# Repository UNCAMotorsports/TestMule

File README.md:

# RedBuggy
Software related to the "Red Buggy" / FSAE car for UNCA Motorsports

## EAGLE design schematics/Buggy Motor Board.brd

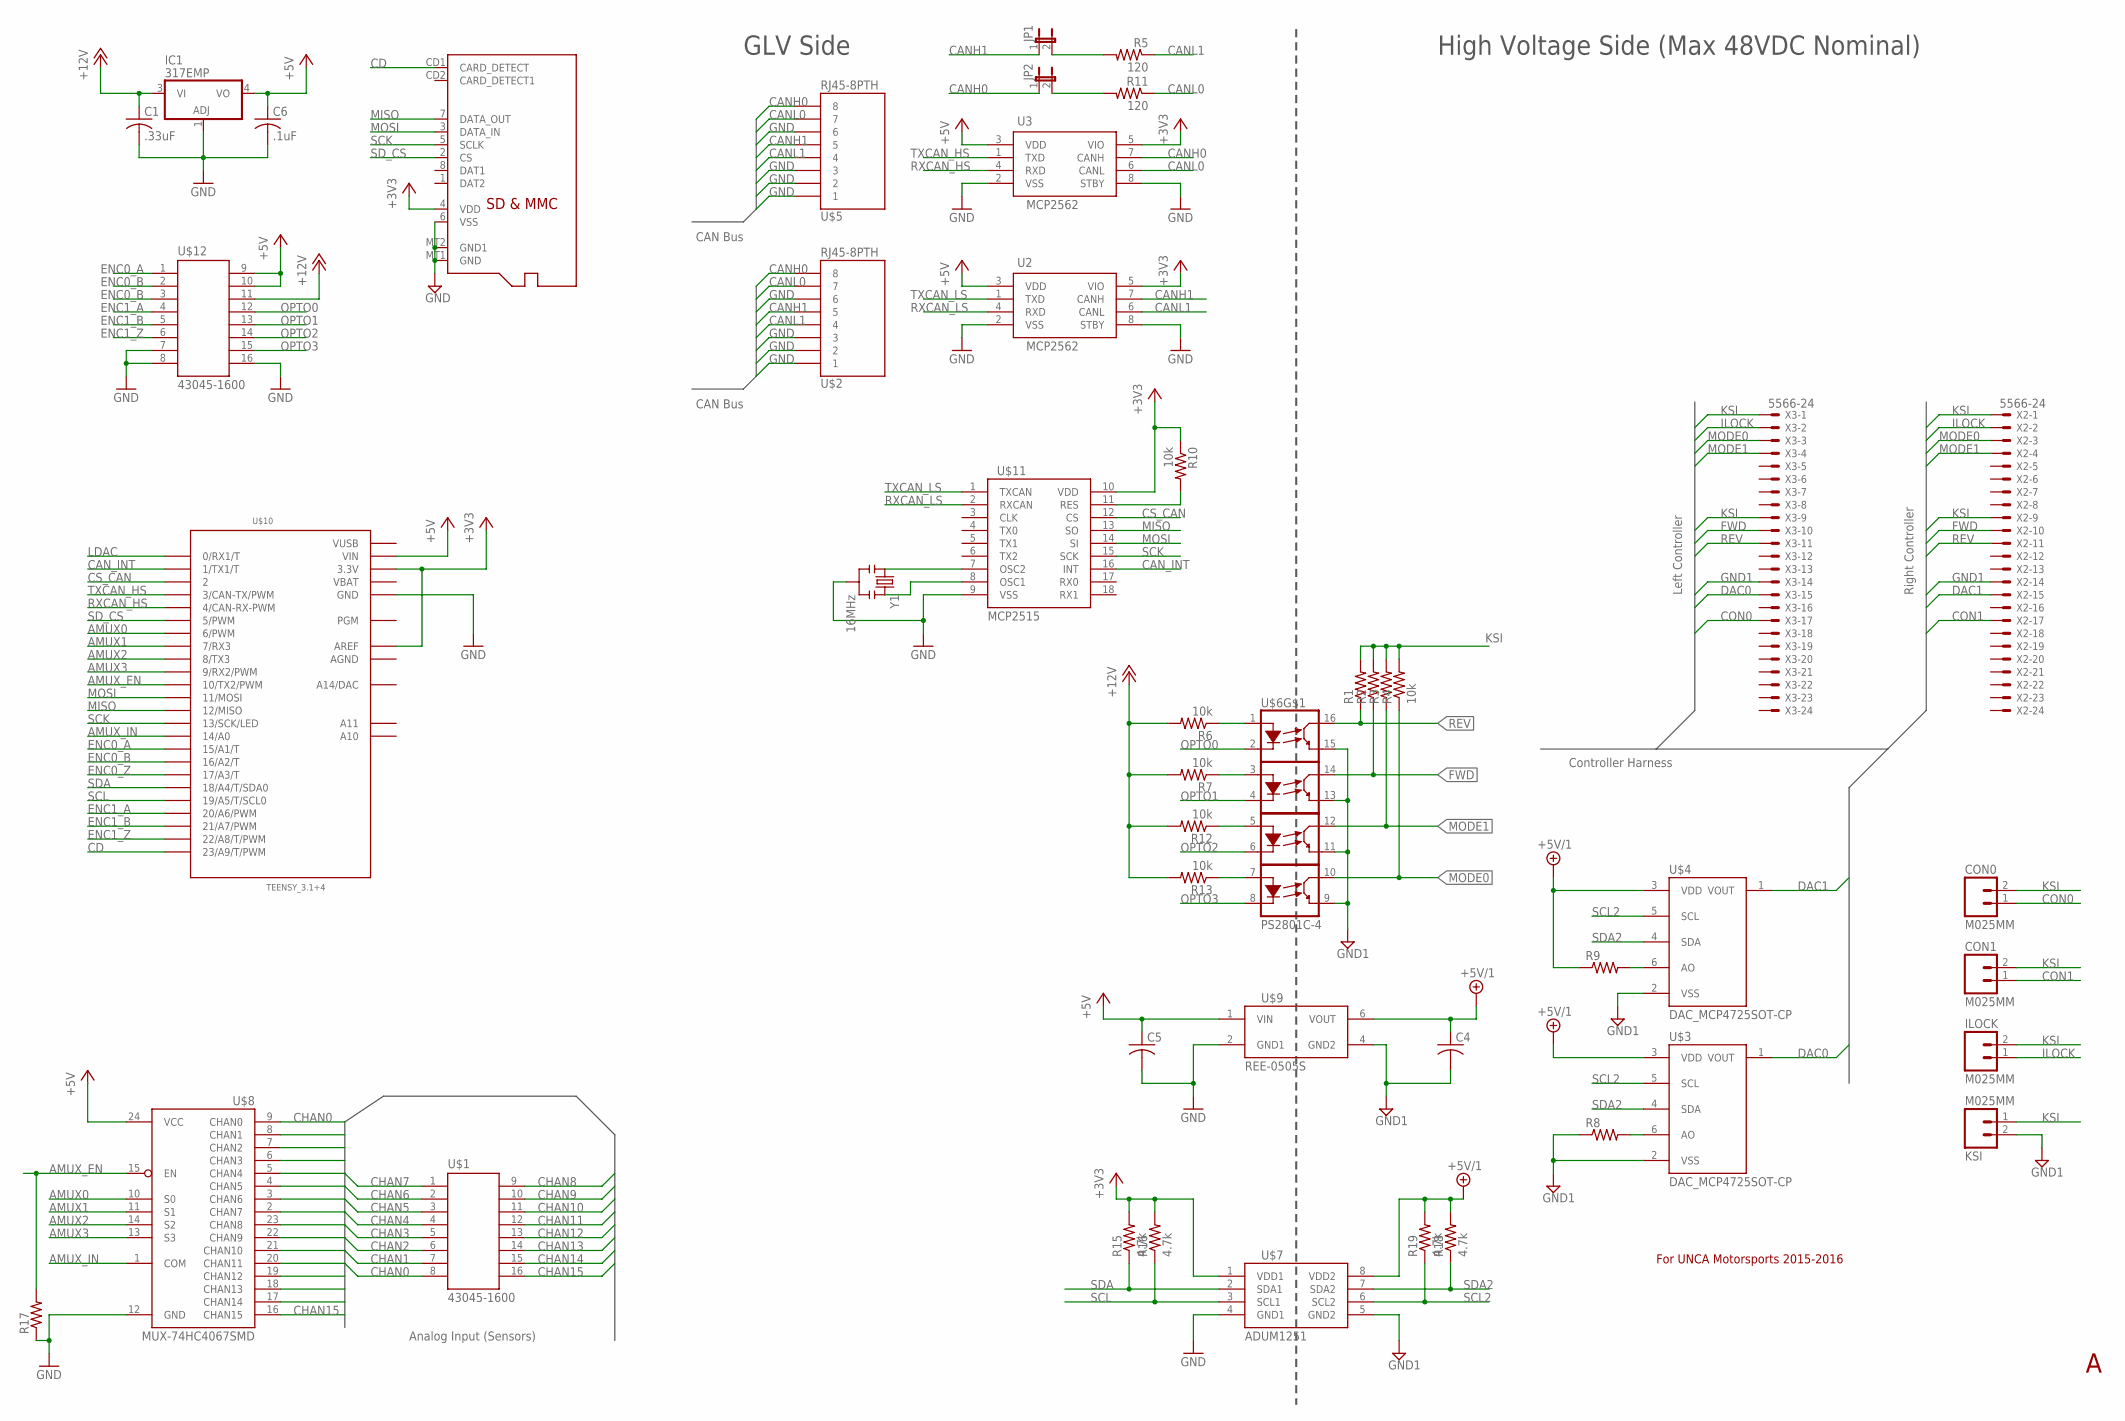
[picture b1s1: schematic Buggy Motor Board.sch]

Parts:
C1: .33uF; C0805
C4, C5: C-USC1210K; C1210K
C6: .1uF; C0805
CON0, CON1: M025MM; SCREWTERMINAL-5MM-2
IC1: 317EMP; SOT223
ILOCK: M025MM; SCREWTERMINAL-5MM-2
JP1, JP2: JP1E; JP1
KSI: M025MM; SCREWTERMINAL-5MM-2
R1, R2, R3, R8, R9, R17: RESISTOR0805-RES; 0805
R4, R6, R7, R10, R12, R13: 10k; 0805
R5, R11: 120; 0805
R15, R16, R18, R19: 4.7k; 0805
U2, U3: MCP2562; SO08
U$1, U$12: 43045-1600
U$2, U$5: RJ45-8PTH; RJ45-8
U$3, U$4: DAC_MCP4725SOT-CP; SOT23-6-MCP4725
U$6: PS2801C-4; 16-SOIC
U$7: ADUM1251; 8-SOIC
U$8: MUX-74HC4067SMD; SSOP24
U$9: REE-0505S
U$10: TEENSY_3.1+4
U$11: MCP2515; DIL18
X1: MICROSD
X2, X3: 5566-24
Y1: 16MHz; RESONATOR-PTH

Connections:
+3V3: R10.1, R15.2, R16.2, U2.5 (VIO), U3.5 (VIO), U$7.1 (VDD1), U$10.3.3V, U$10.3.3V1 (3.3V), U$10.AREF, U$11.10 (VDD), X1.4 (VDD)
+5V: C5.1, C6.1, IC1.4 (VO), U2.3 (VDD), U3.3 (VDD), U$8.24 (VCC), U$9.1 (VIN), U$10.VIN, U$12.9, U$12.10
+5V/1: C4.1, R9.1, R18.2, R19.2, U$3.3 (VDD), U$4.3 (VDD), U$7.8 (VDD2), U$9.6 (VOUT)
+12V: C1.1, IC1.3 (VI), R6.2, R7.2, R12.2, R13.2, U$12.11
AGND: U$10.AGND
AMUX0: U$8.10 (S0), U$10.6 (6/PWM)
AMUX1: U$8.11 (S1), U$10.7 (7/RX3)
AMUX2: U$8.14 (S2), U$10.8 (8/TX3)
AMUX3: U$8.13 (S3), U$10.9 (9/RX2/PWM)
AMUX_EN: R17.2, U$8.15 (EN), U$10.10 (10/TX2/PWM)
AMUX_IN: U$8.1 (COM), U$10.14/A0
CANH0: JP2.1, U3.7 (CANH), U$2.8, U$5.8
CANH1: JP1.1, U2.7 (CANH), U$2.5, U$5.5
CANL0: R11.1, U3.6 (CANL), U$2.7, U$5.7
CANL1: R5.1, U2.6 (CANL), U$2.4, U$5.4
CAN_INT: U$10.1 (1/TX1/T), U$11.16 (INT)
CD: U$10.23/A9 (23/A9/T/PWM), X1.CD1 (CARD_DETECT)
CHAN0: U$1.8, U$8.9 (CHAN0)
CHAN1: U$1.7, U$8.8 (CHAN1)
CHAN2: U$1.6, U$8.7 (CHAN2)
CHAN3: U$1.5, U$8.6 (CHAN3)
CHAN4: U$1.4, U$8.5 (CHAN4)
CHAN5: U$1.3, U$8.4 (CHAN5)
CHAN6: U$1.2, U$8.3 (CHAN6)
CHAN7: U$1.1, U$8.2 (CHAN7)
CHAN8: U$1.9, U$8.23 (CHAN8)
CHAN9: U$1.10, U$8.22 (CHAN9)
CHAN10: U$1.11, U$8.21 (CHAN10)
CHAN11: U$1.12, U$8.20 (CHAN11)
CHAN12: U$1.13, U$8.19 (CHAN12)
CHAN13: U$1.14, U$8.18 (CHAN13)
CHAN14: U$1.15, U$8.17 (CHAN14)
CHAN15: U$1.16, U$8.16 (CHAN15)
CON0: CON0.1, X3.17
CON1: CON1.1, X2.17
CS_CAN: U$10.2, U$11.12 (CS)
DAC0: U$3.1 (VOUT), X3.15
DAC1: U$4.1 (VOUT), X2.15
ENC0_A: U$10.15/A1 (15/A1/T), U$12.1
ENC0_B: U$10.16/A2 (16/A2/T), U$12.2
ENC0_Z: U$10.17/A3 (17/A3/T), U$12.3
ENC1_A: U$10.20/A6 (20/A6/PWM), U$12.4
ENC1_B: U$10.21/A7 (21/A7/PWM), U$12.5
ENC1_Z: U$10.22/A8 (22/A8/T/PWM), U$12.6
FWD: R2.1, U$6.14 (L1), X2.10, X3.10
GND: C1.2, C5.2, C6.2, IC1.1 (ADJ), R17.1, U2.2 (VSS), U2.8 (STBY), U3.2 (VSS), U3.8 (STBY), U$2.1, U$2.2, U$2.3, U$2.6, U$5.1, U$5.2, U$5.3, U$5.6, U$7.4 (GND1), U$8.12 (GND), U$9.2 (GND1), U$10.GND, U$10.GND1 (GND), U$11.9 (VSS), U$12.7, U$12.8, U$12.16, X1.6 (VSS), X1.MT1 (GND), X1.MT2 (GND1), Y1.2
GND1: C4.2, KSI.2, R8.1, U$3.2 (VSS), U$4.2 (VSS), U$6.9 (L2), U$6.11 (L2), U$6.13 (L2), U$6.15 (L2), U$7.5 (GND2), U$9.4 (GND2), X2.14, X3.14
ILOCK: ILOCK.1, X2.2, X3.2
KSI: CON0.2, CON1.2, ILOCK.2, KSI.1, R1.2, R2.2, R3.2, R4.2, X2.1, X2.9, X3.1, X3.9
LDAC: U$10.0 (0/RX1/T)
MISO: U$10.12 (12/MISO), U$11.13 (SO), X1.7 (DATA_OUT)
MODE0: R4.1, U$6.10 (L1), X2.3, X3.3
MODE1: R3.1, U$6.12 (L1), X2.4, X3.4
MOSI: U$10.11 (11/MOSI), U$11.14 (SI), X1.3 (DATA_IN)
unnamed: JP1.2, R5.2
unnamed: R8.2, U$3.6 (AO)
unnamed: R9.2, U$4.6 (AO)
unnamed: U$11.7 (OSC2), Y1.1
unnamed: U$11.8 (OSC1), Y1.3
unnamed: R6.1, U$6.1 (A)
unnamed: JP2.2, R11.2
unnamed: R10.2, U$11.11 (RES)
unnamed: R7.1, U$6.3 (A)
unnamed: R12.1, U$6.5 (A)
unnamed: R13.1, U$6.7 (A)
OPTO0: U$6.2 (C), U$12.12
OPTO1: U$6.4 (C), U$12.13
OPTO2: U$6.6 (C), U$12.14
OPTO3: U$6.8 (C), U$12.15
REV: R1.1, U$6.16 (L1), X2.11, X3.11
RXCAN_HS: U3.4 (RXD), U$10.4 (4/CAN-RX-PWM)
RXCAN_LS: U2.4 (RXD), U$11.2 (RXCAN)
SCK: U$10.13 (13/SCK/LED), U$11.15 (SCK), X1.5 (SCLK)
SCL: R16.1, U$7.3 (SCL1), U$10.19/A5 (19/A5/T/SCL0)
SCL2: R19.1, U$3.5 (SCL), U$4.5 (SCL), U$7.6 (SCL2)
SDA: R15.1, U$7.2 (SDA1), U$10.18/A4 (18/A4/T/SDA0)
SDA2: R18.1, U$3.4 (SDA), U$4.4 (SDA), U$7.7 (SDA2)
SD_CS: U$10.5 (5/PWM), X1.2 (CS)
TXCAN_HS: U3.1 (TXD), U$10.3 (3/CAN-TX/PWM)
TXCAN_LS: U2.1 (TXD), U$11.1 (TXCAN)
VBAT: U$10.VBAT
VUSB: U$10.VUSB

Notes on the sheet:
For UNCA Motorsports 2015-2016
Analog Input (Sensors)
CAN Bus
Controller Harness
Left Controller
Right Controller
High Voltage Side (Max 48VDC Nominal)
GLV Side

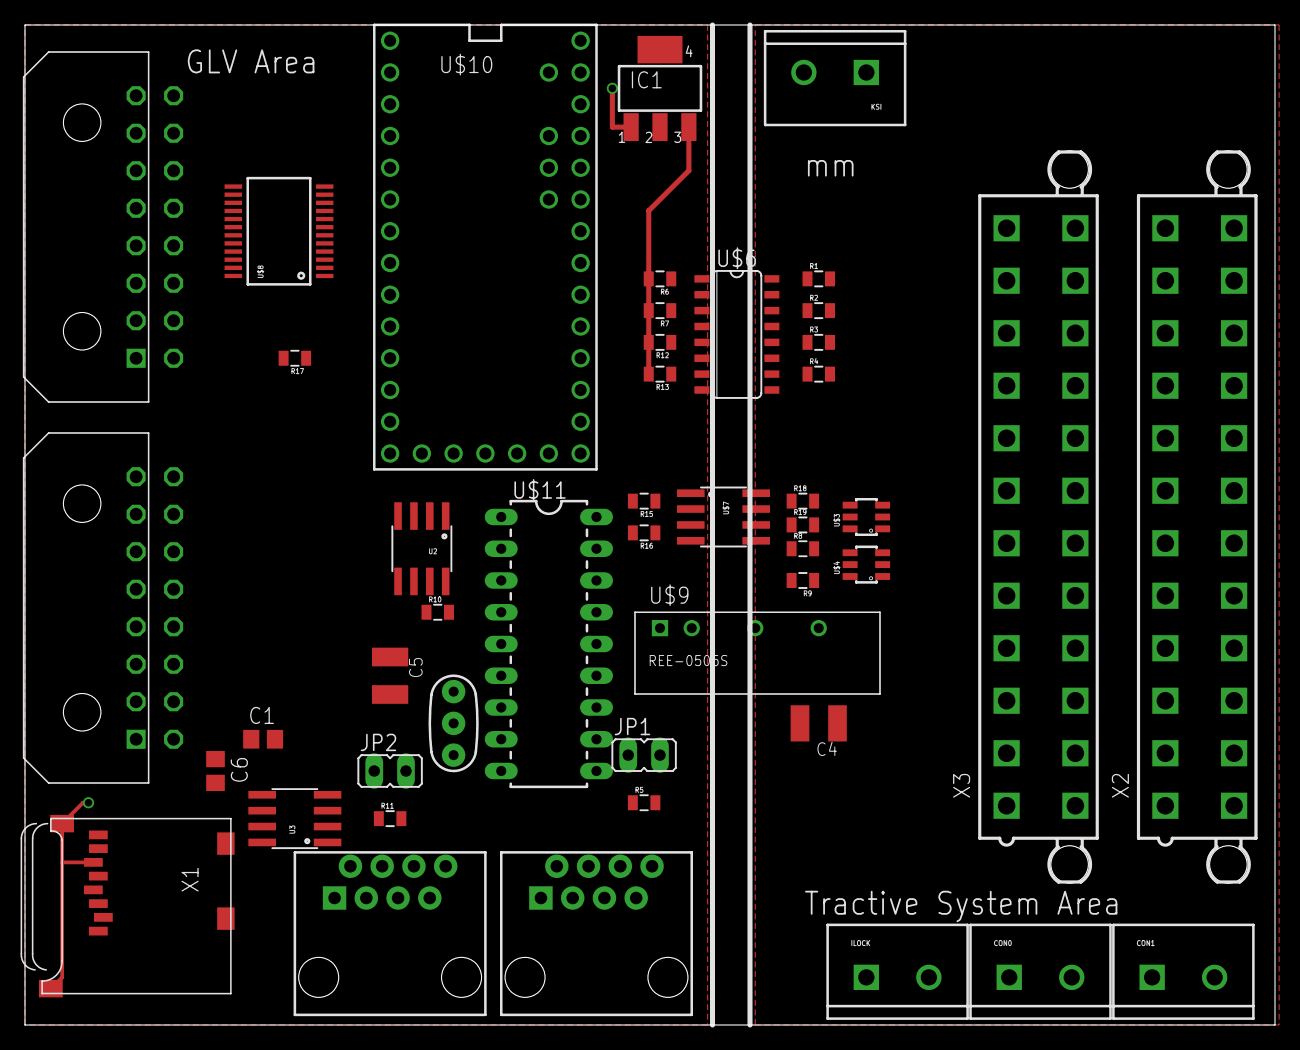
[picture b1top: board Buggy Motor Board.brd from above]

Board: 2 copper layers, 100.0 x 80.0 mm, 47 parts (0 on the bottom side), 78 nets.

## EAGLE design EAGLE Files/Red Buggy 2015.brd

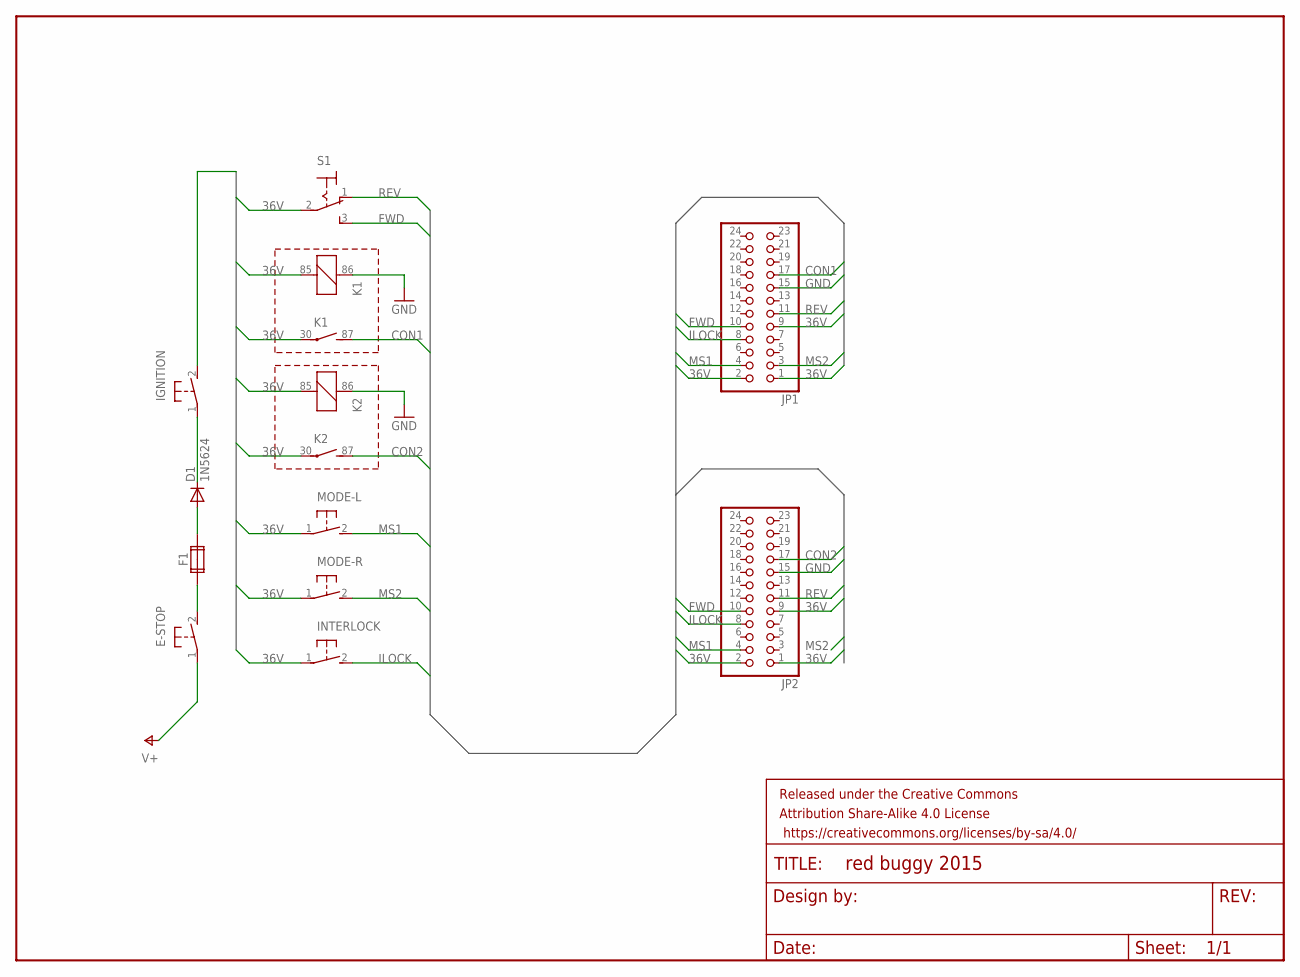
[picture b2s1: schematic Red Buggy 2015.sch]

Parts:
D1: 1N5624; DO201-15
E-STOP: 31-XX; B3F-31XX
F1: FUSE2P; FUSE1
FRAME1: FRAME-LETTER; CREATIVE_COMMONS
IGNITION: 31-XX; B3F-31XX
INTERLOCK: 31-XX; B3F-31XX
JP1, JP2: PINHD-2X12; 2X12
K1, K2: CB1A-P-12V; CB1
MODE-L: 31-XX; B3F-31XX
MODE-R: 31-XX; B3F-31XX
S1: 320-916

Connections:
36V: IGNITION.2 (S), INTERLOCK.1, JP1.1, JP1.2, JP1.9, JP2.1, JP2.2, JP2.9, K1.30, K1.85 (2), K2.30, K2.85 (2), MODE-L.1, MODE-R.1, S1.2
CON1: JP1.17, K1.87 (S)
CON2: JP2.17, K2.87 (S)
FWD: JP1.10, JP2.10, S1.3 (S)
GND: JP1.15, JP2.15, K1.86 (1), K2.86 (1)
ILOCK: INTERLOCK.2 (S), JP1.8, JP2.8
MS1: JP1.4, JP2.4, MODE-L.2 (S)
MS2: JP1.3, MODE-R.2 (S)
unnamed: D1.A, F1.2A
unnamed: E-STOP.2 (S), F1.1A
unnamed: D1.C, IGNITION.1
REV: JP1.11, JP2.11, S1.1 (O)
V+: E-STOP.1

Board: 2 copper layers, 13 parts (0 on the bottom side), 12 nets, no tracks yet.

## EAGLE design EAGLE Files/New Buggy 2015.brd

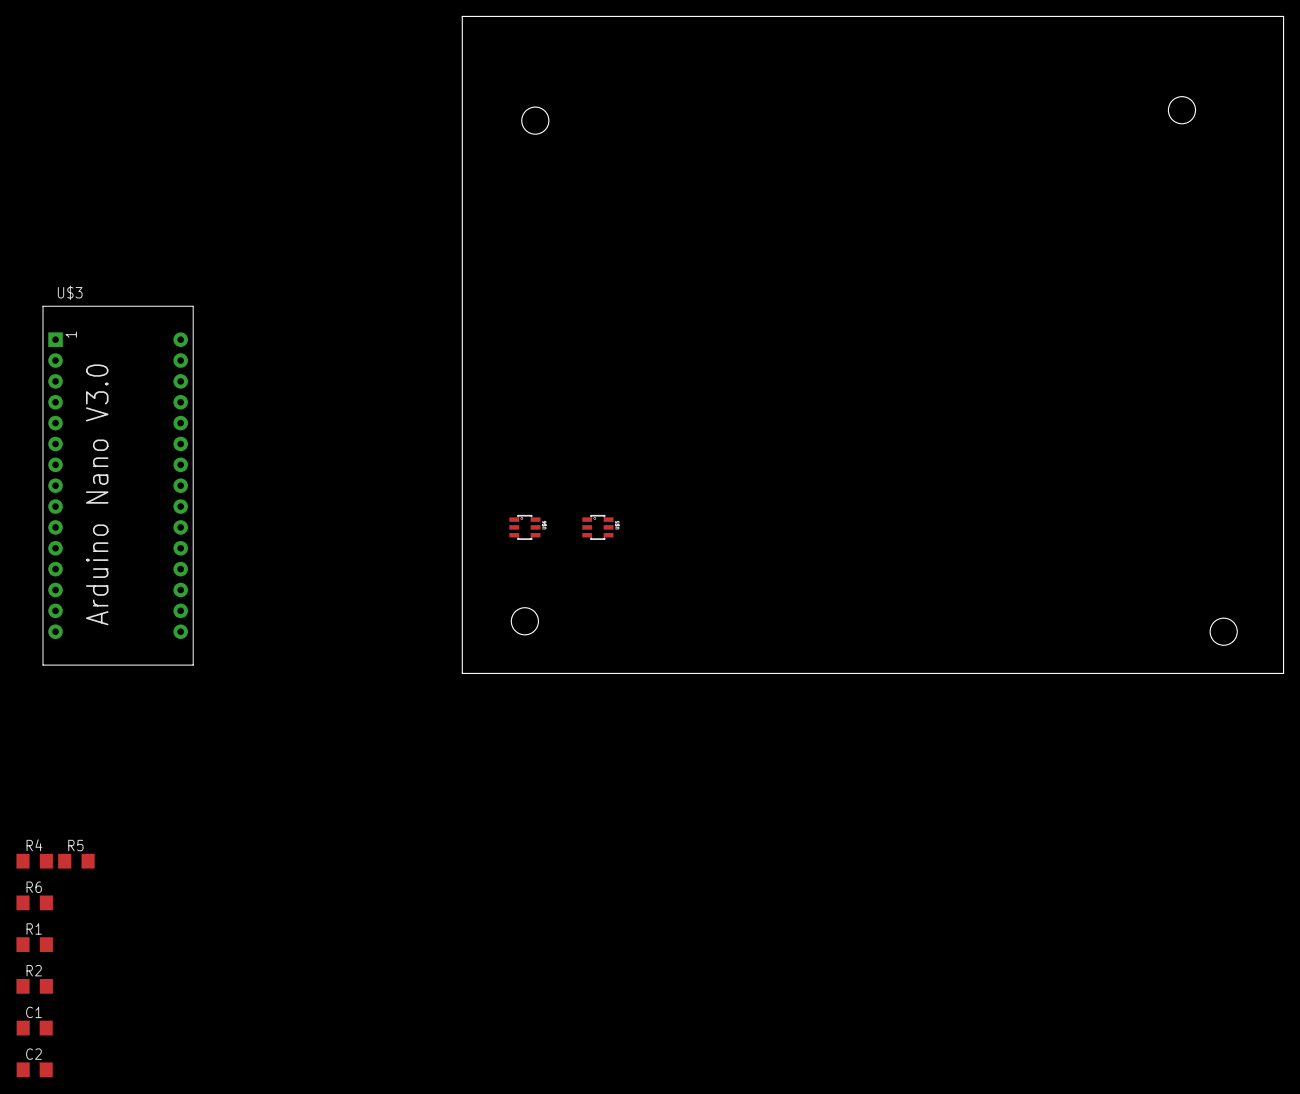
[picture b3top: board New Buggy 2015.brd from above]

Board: 2 copper layers, 100.0 x 80.0 mm, 14 parts (0 on the bottom side), 5 nets, no tracks yet.

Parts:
C1, C2: C1206
R1, R2, R4, R5, R6: R1206
STANDOFF1, STANDOFF2, STANDOFF3, STANDOFF4: STAND-OFF
U$3: ARDUINO_NANO
U$5, U$6: DAC_MCP4725SOT-CP; SOT23-6-MCP4725

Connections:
+5V: C1.1, C2.1, R1.1, R2.1, R4.1, R5.1, R6.1, U$3.+5V, U$5.3, U$6.3
GND: C1.2, C2.2, U$3.GND, U$3.GND@1, U$5.2, U$5.6, U$6.2
unnamed: R6.2, U$6.6
SCL: R1.2, R4.2, U$3.SCL*, U$5.5, U$6.5
SDA: R2.2, R5.2, U$3.SDA, U$5.4, U$6.4

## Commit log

2015-06-26 Actual Initial
2015-06-26 Testing pull requests
2015-06-30 Add sdf to gitignore
2015-06-30 More gitignore
2015-07-04 Add Old Code
2015-07-11 Control System docs init
2015-07-11 EAGLE Schematic init
2015-07-11 Added shift register (TEST)
2015-07-11 Added Screw Clamp (TEST)
2015-07-12 CAN Bus testing (Send/recv)
2015-07-14 CAN implementation
2015-07-20 Add CAN support to schematic, high side drivers.
2015-07-20 Interesting Red Buggy data
2015-07-22 Add SD Card slot & level shifter
2015-07-23 SourceTree test with Github
2015-07-24 Add analog multiplexer, shift register
2015-07-24 Add frame
2015-07-24 Optoisolators, MPU9150, cleanup
2015-07-24 Second shift register
2015-07-25 Saved with 25-07-2015 Visual Micro
2015-07-26 Second optocoupler
2015-07-26 Add molex connectors for curtis controllers
2015-07-27 Organization
2015-07-28 Tweak for Red Buggy
    Removed IMU, second opto-coupler, shift registers; added connectors for
    Curtis motor controllers
2015-07-28 Fix Libraries
2015-07-28 Rebuild
2015-07-29 Start Board, improve isolation
    Started layout of board. Changed Optocoupler. Improved isolation by
    moving DACs to the high voltage side and providing an isolated 5v rail.
    Added Isolated I2C Converter to communicate with DACs across airgap.
2015-08-02 Power consumption, analog input connectors
2015-08-04 Libraries
2015-08-04 Replace Nano with Teensy 3.1
2015-08-05 Add microfit connector
2015-08-05 Microfit connector
2015-08-06 Tweaks
2015-08-07 5v Optocoupling
2015-09-07 Pre-Share Update
2015-09-07 Demo
2015-09-08 Upgrade to newest Visual Micro
2015-09-08 Remove 3v3 level shifter, add encoder inputs
2015-09-08 Remove legacy code
    Code was a cluster of outdated Visual Micro, etc. CLeaning up.
2015-09-08 Move some stuff around
2015-09-08 Moving
2015-09-08 Add *.b#* to gitignore
2015-09-08 Tweak for Master
2015-09-08 Add Quadrature Counter, RTC, MPU, CAN Bus 2
2015-09-12 Schematic changes
2015-09-12 gitIgnore
2015-09-12 remove sdf
2015-09-12 Implement steering code
2015-09-12 Comments, latch
2015-09-20 Teensy changes, working code
2015-09-26 Debug defines
2015-10-18 Tested to be working with motors
2016-02-12 Fix DAC_MCP49xx
2016-03-02 Commit working code
2016-03-02 Add Simple Constrain, profiling code, intterupt on change
2016-03-02 Fix Encoder conversion
2016-03-02 Move steering into its own function
2016-03-03 Minor loop timing fixes
2016-03-03 Add getThrottle(int)
2016-03-06 Set Enc pins as inputs
2016-03-06 Add FlexCAN, vehicle class
2016-03-06 Fix SLN
2016-03-07 Update to working code
2016-03-07 Setup encoder inputs
2016-03-13 Remove extraneous files
2016-03-13 Flexcan is a default lib...
2016-03-13 Library fixes, comments
2016-03-13 Create MuleThrottle, refactor
2016-03-20 Compiled files
2016-03-26 Fix some debug formatting
2016-03-26 Don't track VS data
2016-03-26 Remove binaries and hard to track files
2016-03-26 Add more to gitignore
2016-03-26 Finally...
2016-03-26 Test on Mule, fix SD
2016-03-31 Start Torque Vectoring code
2016-03-31 Implement Torque Vectoring
2016-03-31 Add Data logging, torque vectoring
2016-04-09 Sensor & logging tweaks
2016-04-09 Refactor code - multi-rate main loop
2016-04-11 Fixes to get new code working correctly
2016-04-16 Mule Defines, back to counting pulses for RPM
2016-04-17 Changes to MuleDefines
2016-05-25 Faster Data Logging (block writes)
2016-05-25 Actually use the array of buffers...
2016-05-28 Add data Version
2016-08-16 Enable Debug
2016-08-16 More Debug
2016-08-17 Update to 24000 blocks
2016-08-17 Working Python Data Parser for version 1
2016-08-18 Add Global Clock, fix steerAngle error
2016-08-18 RPM Smoothing
2016-08-18 Fix python script
2016-08-23 Moving avg filter of speed
2016-08-23 Final testing for new Datalogging
2016-08-23 Logging Switch
2016-08-25 Add new 600ppr left encoder
2016-08-25 Tested new encoder
2016-08-25 Stop RPM debug
2016-08-25 Ifdef for logging
2016-08-26 Throttle Warnings, new RH encoder PPR, input_pullup
2016-08-31 Disable Differential
2016-08-31 Add data
2016-09-04 Increase Serial speed to 250000
2016-09-04 Add SPI.h, working
2016-09-07 Remove SPI.h
2016-09-25 Added MCP47FEBXX datasheet (dual i2c dac)
2016-10-24 CAN Testing OK
2016-10-25 Add canheader, canhandler
2016-10-30 Vehicle driving on CAN

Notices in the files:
parts and their libraries:
SparkFun-Connectors: Licensing: Creative Commons ShareAlike 4.0 International - https://creativecommons.org/licenses/by-sa/4.0
SparkFun-Aesthetics: Released under the Creative Commons Attribution Share-Alike 4.0 License
SparkFun-Aesthetics: https://creativecommons.org/licenses/by-sa/4.0
